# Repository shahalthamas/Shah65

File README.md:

## Shah65
A custom 65% compact, minimalist, aesthetic & cute mechanical keyboard, Uses RP2040 as the MCU and Kalih Hot-swapable sockets.

65% layout
Hot-Swappable Switches
Middle Type C port
Lock and Snap in fit Case

### Schematic

### PCB

### 3D case
Onshape: [Link](https://cad.onshape.com/documents/f1803f145455ec0103fb0303/w/ed14bef00e1f0e3e76f49260/e/63a18fe0a0e5d5b9d507f784?renderMode=0&uiState=6b055399905bbdc01cb6fa95)

### BOM

| PART | TYPE | QUANTITY | UNIT PRICE (USD) | LINE TOTAL (USD) | LINK | VENDOR | Funding | Notes |
|---|---|---:|---:|---:|---|---|---|---|
| Shah65_v2_Y4 | PCB | 5 | $8.96 | $44.80 | [JLCPCB](https://jlcpcb.com/) | JLCPCB | Grant | Order Y4-13855454A; green, 1.6 mm thickness, OSP; shipping excluded. |
| Shah65_v2_Y4 | PCB | 2 | $27.12 | $54.24 | [JLCPCB](https://jlcpcb.com/) | JLCPCB | Grant | SMT026112263954-138...; assemble bottom side; shipping excluded. |
| Akko Botany Switch Pack (45) | Part | 2 | $12.94 | $25.88 | [Stackskb](https://stackskb.com/store/akko-botany-switch-pack-of-45/) | Stackskb | Already own | INR converted at 1 INR = $0.01079 (2026-11-20). |
| Sikakeyb Doubleshot PBT Keycaps (Two Tone White and Green) | Part | 1 | $23.74 | $23.74 | [Stackskb](https://stackskb.com/store/sikakeyb-doubleshot-pbt-keycaps-two-tone-white-and-green/) | Stackskb | Grant | INR converted at 1 INR = $0.01079 (2026-11-20). |
| Shipping | Shipping | 1 | $2.00 | $2.00 |  | Stackskb | Grant | |
| **Total** |  |  |  | **$150.66** |  |  |  |  |
| **Grant total** |  |  |  | **$124.78** |  |  |  |  |

Download the [BOM as CSV](BOM.csv).

### License
[MIT LICENSE](/LICENSE)

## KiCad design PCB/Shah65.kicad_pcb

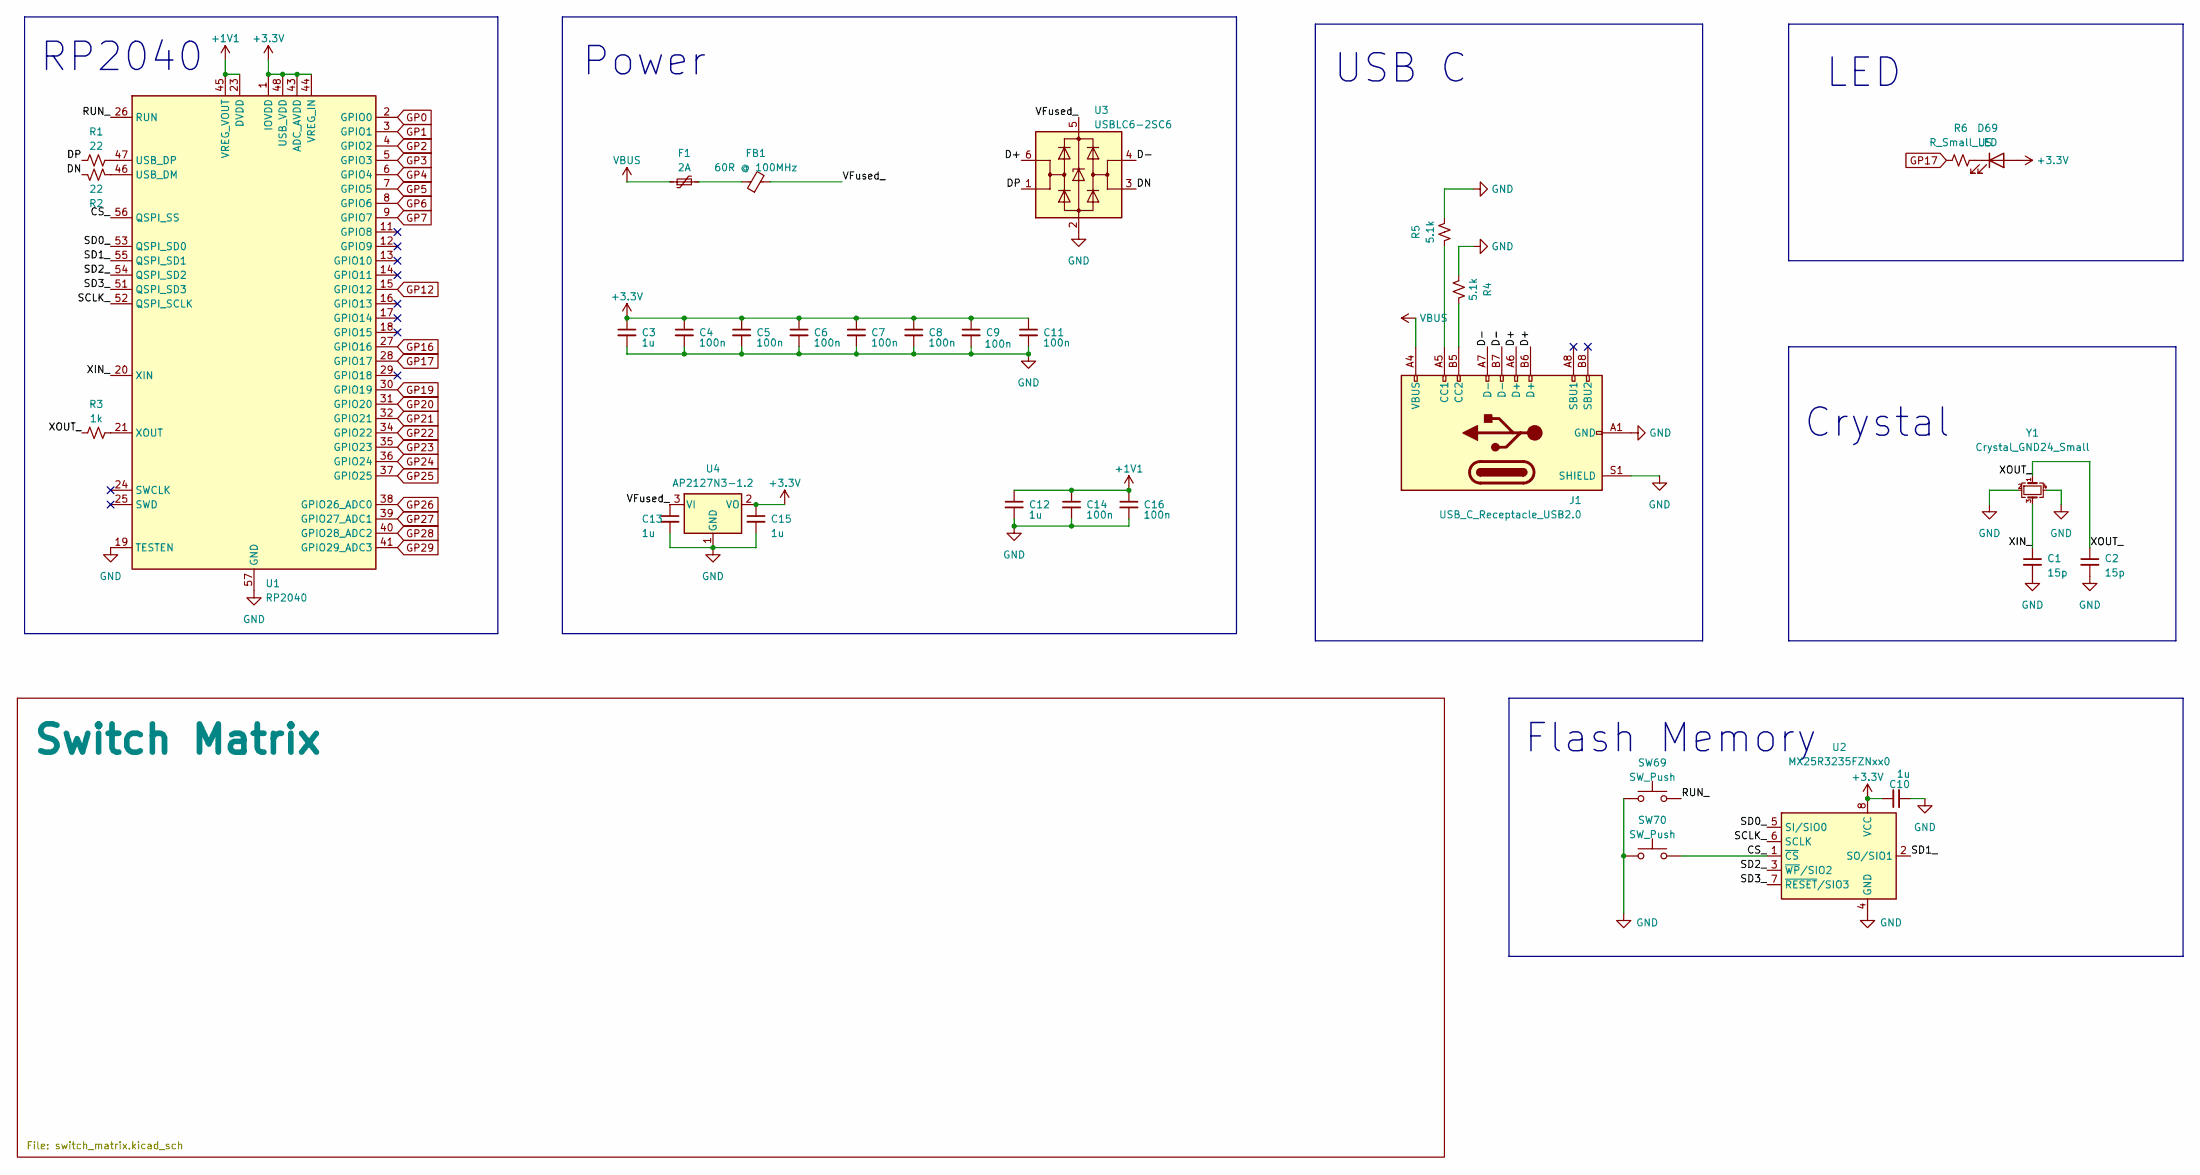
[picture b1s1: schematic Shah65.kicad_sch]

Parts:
C1, C2: 15p; C_0603_1608Metric
C3, C10, C12, C13, C15: 1u; C_0603_1608Metric
C4, C5, C6, C7, C8, C9, C11, C14, C16: 100n; C_0603_1608Metric
D69: LED; LED_MX_3mm
F1: 2A; Fuse_0603_1608Metric_Pad1.05x0.95mm_HandSolder
FB1: 60R @ 100MHz; L_0603_1608Metric
J1: USB_C_Receptacle_USB2.0; USB_C_Receptacle_HRO_TYPE-C-31-M-12
R1, R2: 22; R_0402_1005Metric
R3: 1k; R_0402_1005Metric
R4, R5: 5.1k; R_0402_1005Metric
R6: R_Small_US; R_0402_1005Metric; LCSC C25082
SW69, SW70: SW_Push; SW_SPST_SKQG_WithoutStem
U1: RP2040; QFN-56-1EP_7x7mm_P0.4mm_EP3.2x3.2mm_ThermalVias
U2: MX25R3235FZNxx0; SOP-8_3.76x4.96mm_P1.27mm
U3: USBLC6-2SC6; SOT-23-6
U4: AP2127N3-1.2; TSOT-23
Y1: Crystal_GND24_Small; Crystal_SMD_2520-4Pin_2.5x2.0mm

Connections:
+1V1: C12.1, C14.1, C16.1, U1.23 (DVDD), U1.45 (VREG_VOUT), U1.50 (DVDD)
+3.3V: C3.1, C4.1, C5.1, C6.1, C7.1, C8.1, C9.1, C10.1, C11.1, C15.1, D69.2 (A), U1.1 (IOVDD), U1.10 (IOVDD), U1.22 (IOVDD), U1.33 (IOVDD), U1.42 (IOVDD), U1.43 (ADC_AVDD), U1.44 (VREG_IN), U1.48 (USB_VDD), U1.49 (IOVDD), U2.8 (VCC), U4.2 (VO)
/CS_: SW70.2, U1.56 (QSPI_SS), U2.1 (~CS)
/D+: J1.A6 (D+), J1.B6 (D+), U3.6 (I/O1)
/D-: J1.A7 (D-), J1.B7 (D-), U3.4 (I/O2)
/DN: R2.2, U3.3 (I/O2)
/DP: R1.1, U3.1 (I/O1)
/RUN_: SW69.2, U1.26 (RUN)
/SCLK_: U1.52 (QSPI_SCLK), U2.6 (SCLK)
/SD0_: U1.53 (QSPI_SD0), U2.5 (SI/SIO0)
/SD1_: U1.55 (QSPI_SD1), U2.2 (SO/SIO1)
/SD2_: U1.54 (QSPI_SD2), U2.3 (~WP/SIO2)
/SD3_: U1.51 (QSPI_SD3), U2.7 (~RESET/SIO3)
/VFused_: C13.1, FB1.2, U3.5 (VBUS), U4.3 (VI)
/XIN_: C1.1, U1.20 (XIN), Y1.3
/XOUT_: C2.1, R3.1, Y1.1
GND: C1.2, C2.2, C3.2, C4.2, C5.2, C6.2, C7.2, C8.2, C9.2, C10.2, C11.2, C12.2, C13.2, C14.2, C15.2, C16.2, J1.A1 (GND), J1.A12 (GND), J1.B1 (GND), J1.B12 (GND), J1.S1 (SHIELD), R4.2, R5.1, SW69.1, SW70.1, U1.19 (TESTEN), U1.57 (GND), U2.4 (GND), U2.9 (GND), U3.2 (GND), U4.1 (GND), Y1.2, Y1.4
GP0: U1.2 (GPIO0); also elsewhere on the board
GP1: U1.3 (GPIO1); also elsewhere on the board
GP2: U1.4 (GPIO2); also elsewhere on the board
GP3: U1.5 (GPIO3); also elsewhere on the board
GP4: U1.6 (GPIO4); also elsewhere on the board
GP5: U1.7 (GPIO5); also elsewhere on the board
GP6: U1.8 (GPIO6); also elsewhere on the board
GP7: U1.9 (GPIO7); also elsewhere on the board
GP12: U1.15 (GPIO12); also elsewhere on the board
GP16: U1.27 (GPIO16)
GP17: R6.2, U1.28 (GPIO17)
GP19: U1.30 (GPIO19); also elsewhere on the board
GP20: U1.31 (GPIO20); also elsewhere on the board
GP21: U1.32 (GPIO21); also elsewhere on the board
GP22: U1.34 (GPIO22); also elsewhere on the board
GP23: U1.35 (GPIO23); also elsewhere on the board
GP24: U1.36 (GPIO24); also elsewhere on the board
GP25: U1.37 (GPIO25); also elsewhere on the board
GP26: U1.38 (GPIO26_ADC0); also elsewhere on the board
GP27: U1.39 (GPIO27_ADC1); also elsewhere on the board
GP28: U1.40 (GPIO28_ADC2); also elsewhere on the board
GP29: U1.41 (GPIO29_ADC3); also elsewhere on the board
unnamed: D69.1 (K), R6.1
unnamed: F1.2, FB1.1
unnamed: J1.A5 (CC1), R5.2
unnamed: J1.B5 (CC2), R4.1
unnamed: R2.1, U1.46 (USB_DM)
unnamed: R1.2, U1.47 (USB_DP)
unnamed: R3.2, U1.21 (XOUT)
VBUS: F1.1, J1.A4 (VBUS), J1.A9 (VBUS), J1.B4 (VBUS), J1.B9 (VBUS)

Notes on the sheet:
Flash Memory
Power
LED
Crystal
RP2040
USB C

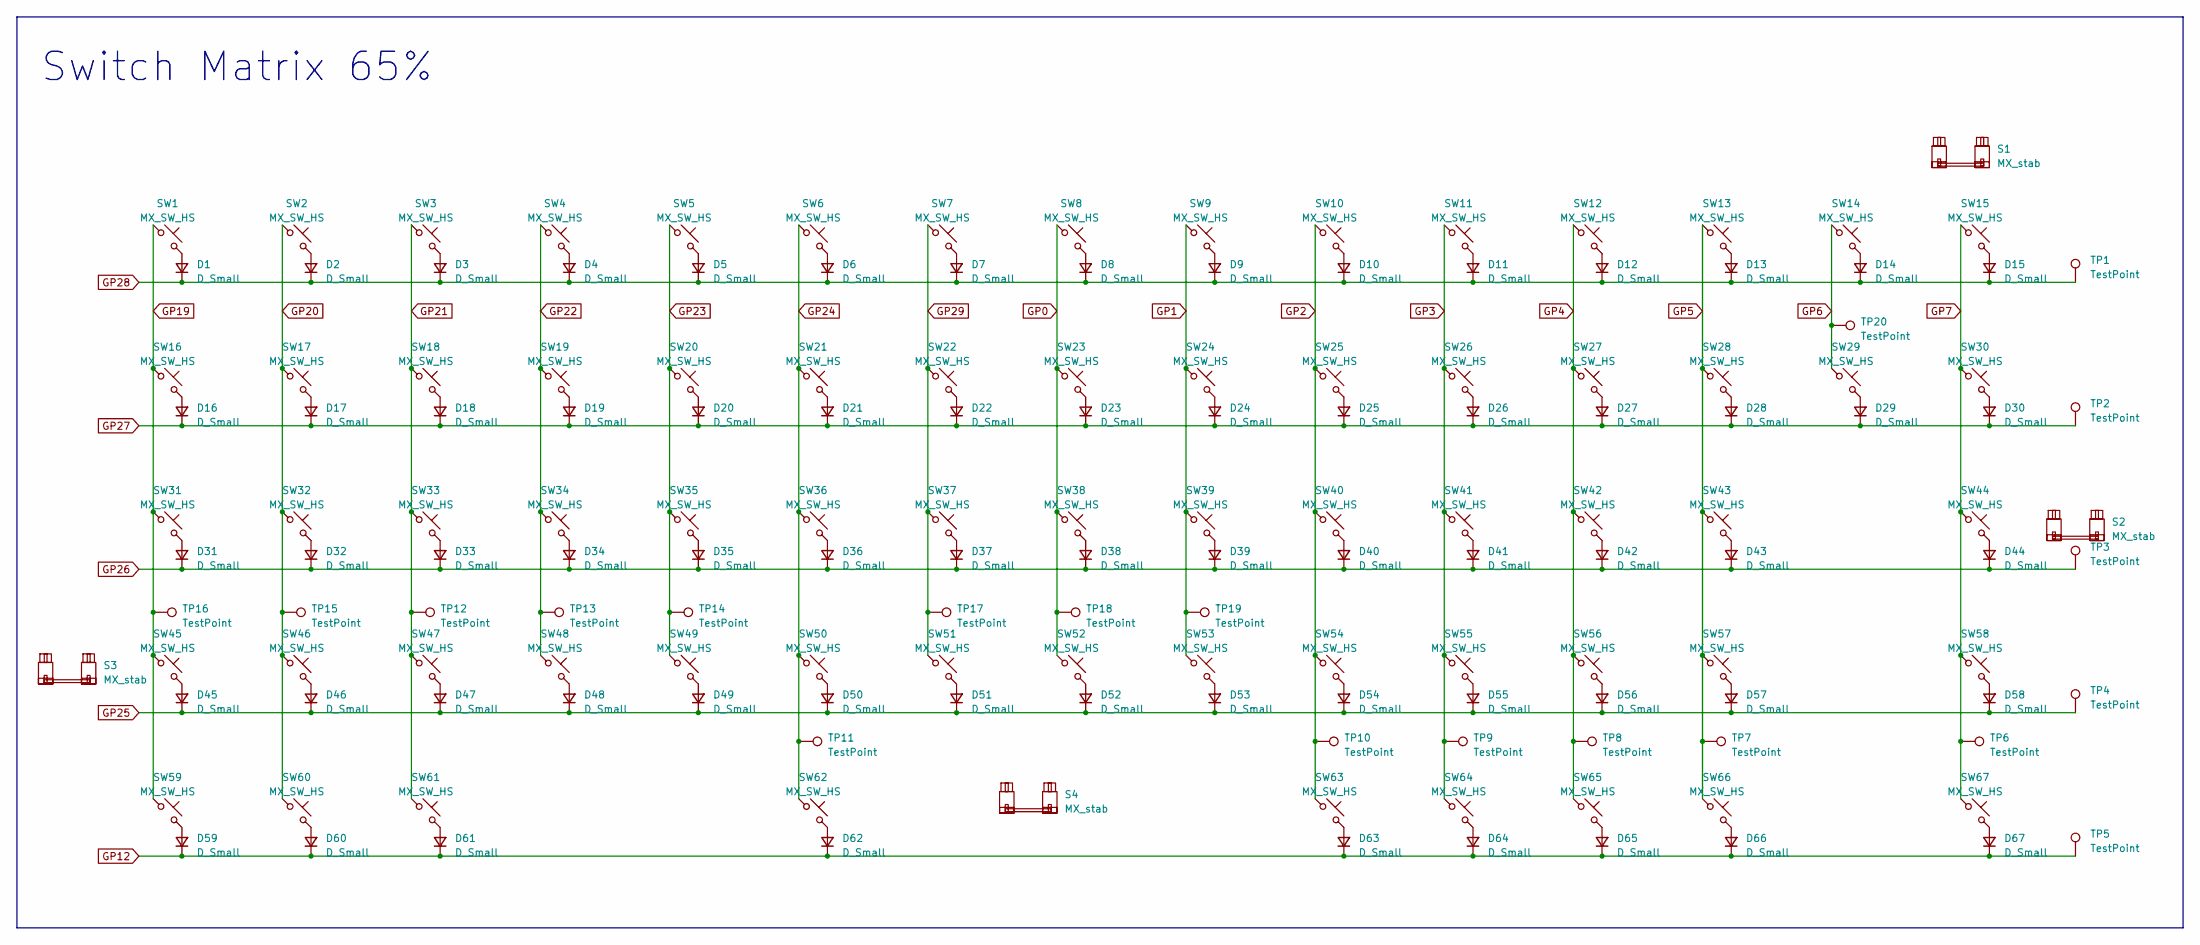
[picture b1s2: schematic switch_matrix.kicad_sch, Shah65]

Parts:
D1, D2, D3, D4, D5, D6, D7, D8, D9, D10, D11, D12, D13, D14, D15, D16, D17, D18, D19, D20, D21, D22, D23, D24, D25, D26, D27, D28, D29, D30, D31, D32, D33, D34, D35, D36, D37, D38, D39, D40, D41, D42, D43, D44, D45, D46, D47, D48, D49, D50, D51, D52, D53, D54, D55, D56, D57, D58, D59, D60, D61, D62, D63, D64, D65, D66, D67: D_Small; D_SOD-123
S1: MX_stab; STAB_MX_P_2u
S2, S3: MX_stab; STAB_MX_P_2.25u
S4: MX_stab; STAB_MX_P_6.25u
SW1, SW2, SW3, SW4, SW5, SW6, SW7, SW8, SW9, SW10, SW11, SW12, SW13, SW14, SW15, SW17, SW18, SW19, SW20, SW21, SW22, SW23, SW24, SW25, SW26, SW27, SW28, SW30, SW32, SW33, SW34, SW35, SW36, SW37, SW38, SW39, SW40, SW41, SW42, SW43, SW44, SW45, SW46, SW47, SW48, SW49, SW50, SW51, SW52, SW53, SW54, SW55, SW57, SW58, SW62, SW65, SW66, SW67: MX_SW_HS; SW_MX_HS_CPG151101S11_1u
SW16, SW29: MX_SW_HS; SW_MX_HS_CPG151101S11_1.5u
SW31, SW56: MX_SW_HS; SW_MX_HS_CPG151101S11_1.75u
SW59, SW60, SW61, SW63, SW64: MX_SW_HS; SW_MX_HS_CPG151101S11_1.25u
TP1, TP2, TP3, TP4, TP5, TP6, TP7, TP8, TP9, TP10, TP11, TP12, TP13, TP14, TP15, TP16, TP17, TP18, TP19, TP20: TestPoint; TestPoint_THTPad_2.0x2.0mm_Drill1.0mm

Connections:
GP0: SW8.1, SW23.1, SW38.1, SW52.1, TP18.1 (1_1); also elsewhere on the board
GP1: SW9.1, SW24.1, SW39.1, SW53.1, TP19.1 (1_1); also elsewhere on the board
GP2: SW10.1, SW25.1, SW40.1, SW54.1, SW63.1, TP10.1 (1_1); also elsewhere on the board
GP3: SW11.1, SW26.1, SW41.1, SW55.1, SW64.1, TP9.1 (1_1); also elsewhere on the board
GP4: SW12.1, SW27.1, SW42.1, SW56.1, SW65.1, TP8.1 (1_1); also elsewhere on the board
GP5: SW13.1, SW28.1, SW43.1, SW57.1, SW66.1, TP7.1 (1_1); also elsewhere on the board
GP6: SW14.1, SW29.1, TP20.1 (1_1); also elsewhere on the board
GP7: SW15.1, SW30.1, SW44.1, SW58.1, SW67.1, TP6.1 (1_1); also elsewhere on the board
GP12: D59.1 (K), D60.1 (K), D61.1 (K), D62.1 (K), D63.1 (K), D64.1 (K), D65.1 (K), D66.1 (K), D67.1 (K), TP5.1 (1_1); also elsewhere on the board
GP19: SW1.1, SW16.1, SW31.1, SW45.1, SW59.1, TP16.1 (1_1); also elsewhere on the board
GP20: SW2.1, SW17.1, SW32.1, SW46.1, SW60.1, TP15.1 (1_1); also elsewhere on the board
GP21: SW3.1, SW18.1, SW33.1, SW47.1, SW61.1, TP12.1 (1_1); also elsewhere on the board
GP22: SW4.1, SW19.1, SW34.1, SW48.1, TP13.1 (1_1); also elsewhere on the board
GP23: SW5.1, SW20.1, SW35.1, SW49.1, TP14.1 (1_1); also elsewhere on the board
GP24: SW6.1, SW21.1, SW36.1, SW50.1, SW62.1, TP11.1 (1_1); also elsewhere on the board
GP25: D45.1 (K), D46.1 (K), D47.1 (K), D48.1 (K), D49.1 (K), D50.1 (K), D51.1 (K), D52.1 (K), D53.1 (K), D54.1 (K), D55.1 (K), D56.1 (K), D57.1 (K), D58.1 (K), TP4.1 (1_1); also elsewhere on the board
GP26: D31.1 (K), D32.1 (K), D33.1 (K), D34.1 (K), D35.1 (K), D36.1 (K), D37.1 (K), D38.1 (K), D39.1 (K), D40.1 (K), D41.1 (K), D42.1 (K), D43.1 (K), D44.1 (K), TP3.1 (1_1); also elsewhere on the board
GP27: D16.1 (K), D17.1 (K), D18.1 (K), D19.1 (K), D20.1 (K), D21.1 (K), D22.1 (K), D23.1 (K), D24.1 (K), D25.1 (K), D26.1 (K), D27.1 (K), D28.1 (K), D29.1 (K), D30.1 (K), TP2.1 (1_1); also elsewhere on the board
GP28: D1.1 (K), D2.1 (K), D3.1 (K), D4.1 (K), D5.1 (K), D6.1 (K), D7.1 (K), D8.1 (K), D9.1 (K), D10.1 (K), D11.1 (K), D12.1 (K), D13.1 (K), D14.1 (K), D15.1 (K), TP1.1 (1_1); also elsewhere on the board
GP29: SW7.1, SW22.1, SW37.1, SW51.1, TP17.1 (1_1); also elsewhere on the board
unnamed: D1.2 (A), SW1.2
unnamed: D2.2 (A), SW2.2
unnamed: D3.2 (A), SW3.2
unnamed: D4.2 (A), SW4.2
unnamed: D5.2 (A), SW5.2
unnamed: D6.2 (A), SW6.2
unnamed: D7.2 (A), SW7.2
unnamed: D8.2 (A), SW8.2
unnamed: D9.2 (A), SW9.2
unnamed: D10.2 (A), SW10.2
unnamed: D11.2 (A), SW11.2
unnamed: D12.2 (A), SW12.2
unnamed: D13.2 (A), SW13.2
unnamed: D14.2 (A), SW14.2
unnamed: D15.2 (A), SW15.2
unnamed: D16.2 (A), SW16.2
unnamed: D17.2 (A), SW17.2
unnamed: D18.2 (A), SW18.2
unnamed: D19.2 (A), SW19.2
unnamed: D20.2 (A), SW20.2
unnamed: D21.2 (A), SW21.2
unnamed: D22.2 (A), SW22.2
unnamed: D23.2 (A), SW23.2
unnamed: D24.2 (A), SW24.2
unnamed: D25.2 (A), SW25.2
unnamed: D26.2 (A), SW26.2
unnamed: D27.2 (A), SW27.2
unnamed: D28.2 (A), SW28.2
unnamed: D29.2 (A), SW29.2
unnamed: D30.2 (A), SW30.2
unnamed: D31.2 (A), SW31.2
unnamed: D32.2 (A), SW32.2
unnamed: D33.2 (A), SW33.2
unnamed: D34.2 (A), SW34.2
unnamed: D35.2 (A), SW35.2
unnamed: D36.2 (A), SW36.2
unnamed: D37.2 (A), SW37.2
unnamed: D38.2 (A), SW38.2
unnamed: D39.2 (A), SW39.2
unnamed: D40.2 (A), SW40.2
unnamed: D41.2 (A), SW41.2
unnamed: D42.2 (A), SW42.2
unnamed: D43.2 (A), SW43.2
unnamed: D44.2 (A), SW44.2
unnamed: D45.2 (A), SW45.2
unnamed: D46.2 (A), SW46.2
unnamed: D47.2 (A), SW47.2
unnamed: D48.2 (A), SW48.2
unnamed: D49.2 (A), SW49.2
unnamed: D50.2 (A), SW50.2
unnamed: D51.2 (A), SW51.2
unnamed: D52.2 (A), SW52.2
unnamed: D53.2 (A), SW53.2
unnamed: D54.2 (A), SW54.2
unnamed: D55.2 (A), SW55.2
unnamed: D56.2 (A), SW56.2
unnamed: D57.2 (A), SW57.2
unnamed: D58.2 (A), SW58.2
unnamed: D59.2 (A), SW59.2
unnamed: D60.2 (A), SW60.2
unnamed: D61.2 (A), SW61.2
unnamed: D62.2 (A), SW62.2
unnamed: D63.2 (A), SW63.2
unnamed: D64.2 (A), SW64.2
unnamed: D65.2 (A), SW65.2
unnamed: D66.2 (A), SW66.2
unnamed: D67.2 (A), SW67.2

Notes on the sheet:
Switch Matrix 65%

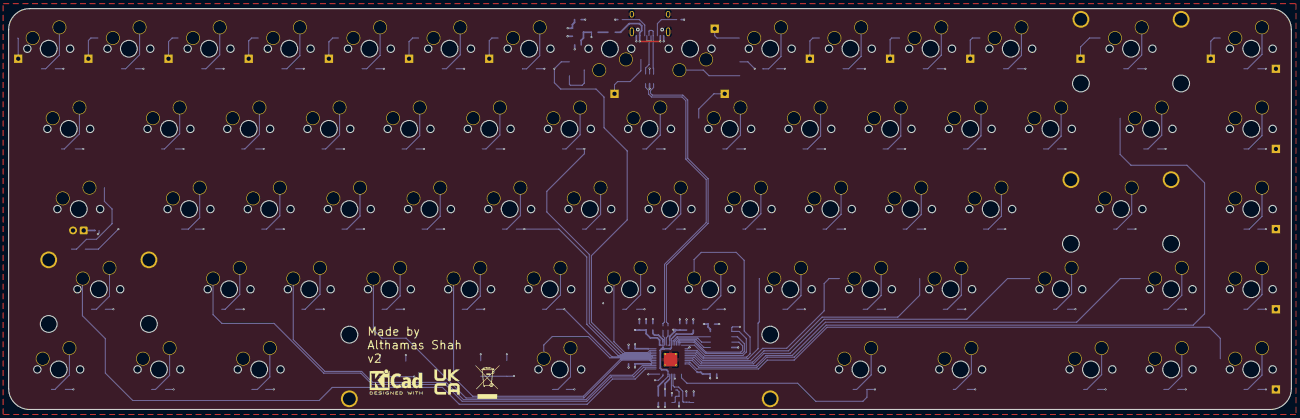
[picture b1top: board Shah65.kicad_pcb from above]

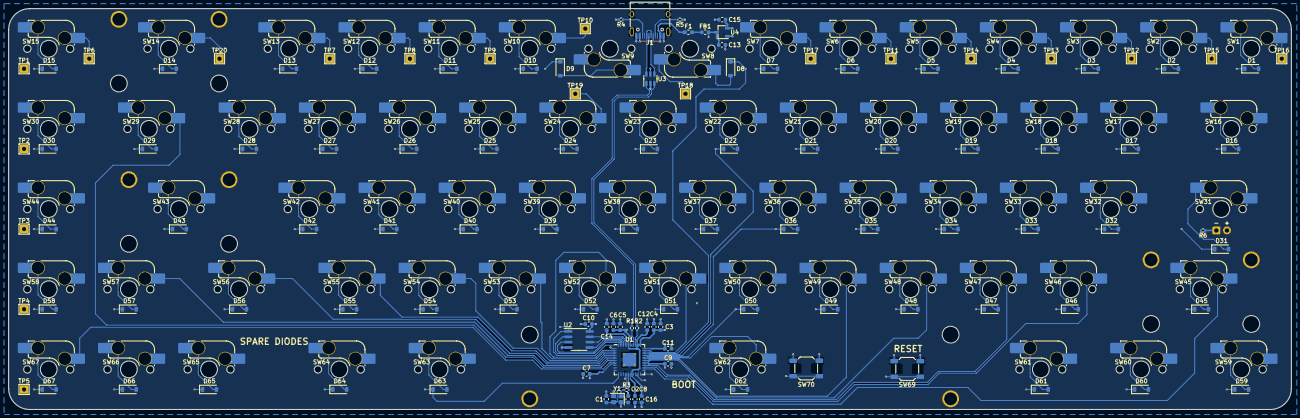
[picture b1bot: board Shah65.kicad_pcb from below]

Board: 4 copper layers, 304.8 x 95.2 mm, 191 parts (186 on the bottom side), 113 nets.

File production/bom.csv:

Designator,Footprint,Quantity,Value,LCSC Part #
"C1, C2",0603,2,15p,
"C10, C12, C13, C15, C3",0603,5,1u,
"C11, C14, C16, C4, C5, C6, C7, C8, C9",0603,9,100n,
"D1, D10, D11, D12, D13, D14, D15, D16, D17, D18, D19, D2, D20, D21, D22, D23, D24, D25, D26, D27, D28, D29, D3, D30, D31, D32, D33, D34, D35, D36, D37, D38, D39, D4, D40, D41, D42, D43, D44, D45, D46, D47, D48, D49, D5, D50, D51, D52, D53, D54, D55, D56, D57, D58, D59, D6, D60, D61, D62, D63, D64, D65, D66, D67, D7, D8, D9",D_SOD-123,67,D_Small,
D69,LED_MX_3mm,1,LED,
F1,0603,1,2A,
FB1,0603,1,60R @ 100MHz,
J1,USB_C_Receptacle_HRO_TYPE-C-31-M-12,1,USB_C_Receptacle_USB2.0,
"R1, R2",0402,2,22,
R3,0402,1,1k,
"R4, R5",0402,2,5.1k,
R6,0402,1,R_Small_US,C25082
S1,STAB_MX_P_2u,1,MX_stab,
"S2, S3",STAB_MX_P_2.25u,2,MX_stab,
S4,STAB_MX_P_6.25u,1,MX_stab,
"SW1, SW10, SW11, SW12, SW13, SW14, SW15, SW17, SW18, SW19, SW2, SW20, SW21, SW22, SW23, SW24, SW25, SW26, SW27, SW28, SW3, SW30, SW32, SW33, SW34, SW35, SW36, SW37, SW38, SW39, SW4, SW40, SW41, SW42, SW43, SW44, SW45, SW46, SW47, SW48, SW49, SW5, SW50, SW51, SW52, SW53, SW54, SW55, SW57, SW58, SW6, SW62, SW65, SW66, SW67, SW7, SW8, SW9",SW_MX_HS_CPG151101S11_1u,58,MX_SW_HS,
"SW16, SW29",SW_MX_HS_CPG151101S11_1.5u,2,MX_SW_HS,
"SW31, SW56",SW_MX_HS_CPG151101S11_1.75u,2,MX_SW_HS,
"SW59, SW60, SW61, SW63, SW64",SW_MX_HS_CPG151101S11_1.25u,5,MX_SW_HS,
"SW69, SW70",SW_SPST_SKQG_WithoutStem,2,SW_Push,
"TP1, TP10, TP11, TP12, TP13, TP14, TP15, TP16, TP17, TP18, TP19, TP2, TP20, TP3, TP4, TP5, TP6, TP7, TP8, TP9",TestPoint_THTPad_2.0x2.0mm_Drill1.0mm,20,TestPoint,
U1,QFN-56-1EP_7x7mm_P0.4mm_EP3.2x3.2mm_ThermalVias,1,RP2040,
U2,SOP-8_3.76x4.96mm_P1.27mm,1,MX25R3235FZNxx0,
U3,SOT-23-6,1,USBLC6-2SC6,
U4,TSOT-23,1,AP2127N3-1.2,
Y1,Crystal_SMD_2520-4Pin_2.5x2.0mm,1,Crystal_GND24_Small,
